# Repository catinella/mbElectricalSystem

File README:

#-----------------------------------------------------------------------------------------------------------------------------------
     __  __       _             _     _ _          _____ _           _        _           _   ____            _                 
    |  \/  | ___ | |_ ___  _ __| |__ (_) | _____  | ____| | ___  ___| |_ _ __(_) ___ __ _| | / ___| _   _ ___| |_ ___ _ __ ___  
    | |\/| |/ _ \| __/ _ \| '__| '_ \| | |/ / _ \ |  _| | |/ _ \/ __| __| '__| |/ __/ _` | | \___ \| | | / __| __/ _ \ '_ ` _ \ 
    | |  | | (_) | || (_) | |  | |_) | |   <  __/ | |___| |  __/ (__| |_| |  | | (_| (_| | |  ___) | |_| \__ \ ||  __/ | | | | |
    |_|  |_|\___/ \__\___/|_|  |_.__/|_|_|\_\___| |_____|_|\___|\___|\__|_|  |_|\___\__,_|_| |____/ \__, |___/\__\___|_| |_| |_|
                                                                                                    |___/                       
#-----------------------------------------------------------------------------------------------------------------------------------

Description:
	This project (MBES) aims to realize a generic motorbike electric system you can use on any old motorbike.
	The system manages the following devices:
		- High light and down light
		- Left and right turn indicators
		- Additional (high power) light
		- Horn
		- Neutral, left/right indicators, high/down light... LEDs
		- STOP light
		- Engine start button
		- Motorbike (and engine) OFF switch
		- Decompressor
		- External cockpit power-connector
		- Cockpit's leds

	The system provides the following features
		- Checking for decompressor command
		  The system does not allow the engine to run, before the decompressor command has been activated

		- Direction indicator blinking
		  Common blinking for the yellow indicator

		- Resistor key
		  In order to turn-on the motorbike, the driver must insert a valid resistor key. After the autentication the key
		  can be also removed. It is very usefull for off-road using. 

		- Parking mode
		  To set the motorbike turned-off but with the normal-light-on and the indicators blinking, you have to put the
		  motorbile stopped on its lateral stand, set the engine swith to off, and turn the normal-light on
	
	Security rules:
		- Byke stand
		  if the motorcycle stand is downn when the engine is connected to the wheels, the the engine will be stopped

		- Decompressor command
		  If the motorcycle is running and the driver will push the decompressor command, then the engine will be stopped

Info about this version:
	This branch is based on ESP32 MCU. This chip is a powerful and very low-price device and it allowed me to reduce the PCB
	size. At the moment, I am using the ESP32 devkit device because welder this chip is a bit difficult operation.

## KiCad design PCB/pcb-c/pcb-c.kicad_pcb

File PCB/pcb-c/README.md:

## 1.0 Files

| Files/Directories | Description             |
|-------------------|-------------------------|
| pcb-c.kicad_sch   | Electrical schematic    |
| pcb-c.kicad_pcb   | PCB                     |

(*) This project is covered by the GPL-3. Please, read that file for further information

## 2.0 Description:
This folder contains all files you need to build and/or modify the PCB placed in the rear side of the (DR350) motorbike.
This circuit is a small power stage for the rear turn indicators, brake light, and position light. Because all lights
are available in LED format, the power stage is set to provide maximum 500mA (6W) per device.

## 2.1 Internals:
In order to fit this device into the rear section of the DR350, I tried to reduce the required space as much as possible.
For this reason, conventional fuses have been replaced by [MSMF050](https://www.bourns.com/docs/product-datasheets/mf-msmf.pdf)
PTC Resettable Fuses.

All the power-stage outputs are equivalent, but one of them is dedicated to the motorbike's starter relay. This type of relay
can have a relatively large coil and may generate a significant voltage spike when switched off. For this reason, I added a
[M7 Rectifiers Diode](https://diotec.com/request/datasheet/m1.pdf) as a flyback diode.

## 3.0 PCB Layout
The following image shows the intended final PCB layout.

## 4.0 Connections
The following diagram shows how to build the cables used to connect the PCB to the other motorbike components.

### 4.1 External connectors
In the left side of the scheme you can see the cables you have to connect with the PCB (pcb-b) in the front side of the
motorcycle. The 3-ways cable of them is used to provide the battery energy to main controller device (in the front-side),
for this reason the selected connector is a 
[Receptacle Terminal Housing, 3 Position, 6.3 mm](https://www.te.com/en/product-180941.html) one. The selected FASTON terminals
can support currents up to 25A

The 6 ways cable, in the scheme left side, has to communicate data from the controller device to the rear power stage.
It has to support a very low current. So, I selected a
[2.8mm (.110") series connectors](https://www.corsa-technic.com/item.php?item_id=222&category_id=53&manufacturer_id=44).
They are very common in automotive applications, you can find all the series producted by other vendors. To get a clear
idea of them I post here a drawing of the cables.

### 4.2 Internal connectors
The main internal connector is a typical [10-pin dual-row connector](https://www.molex.com/en-us/products/part-detail/702461004)
PCB-side one, but the associated plug is not the one that is typically one used for the flat cables. In fact, its wires are not
connected to the same port: 5 pins are connected to the 6-ways external connector, and 4 are connected to the power 3-ways cable.
For this reason you need a different connector where you can crimp every pin to a single wires. Te follow math with the requirements:
[MOLEX 10pin plug](https://www.molex.com/en-us/products/part-detail/22552101?display=pdf&utm_source=M2X&utm_medium=api&utm_campaign=api&utm_id=M2X_API?utm_source=M2X&utm_medium=api&utm_campaign=api&utm_id=M2X_API)
[MOLEX contacts](https://www.molex.com/en-us/products/part-detail/16020102?display=pdf&utm_source=M2X&utm_medium=api&utm_campaign=api&utm_id=M2X_API?utm_source=M2X&utm_medium=api&utm_campaign=api&utm_id=M2X_API)

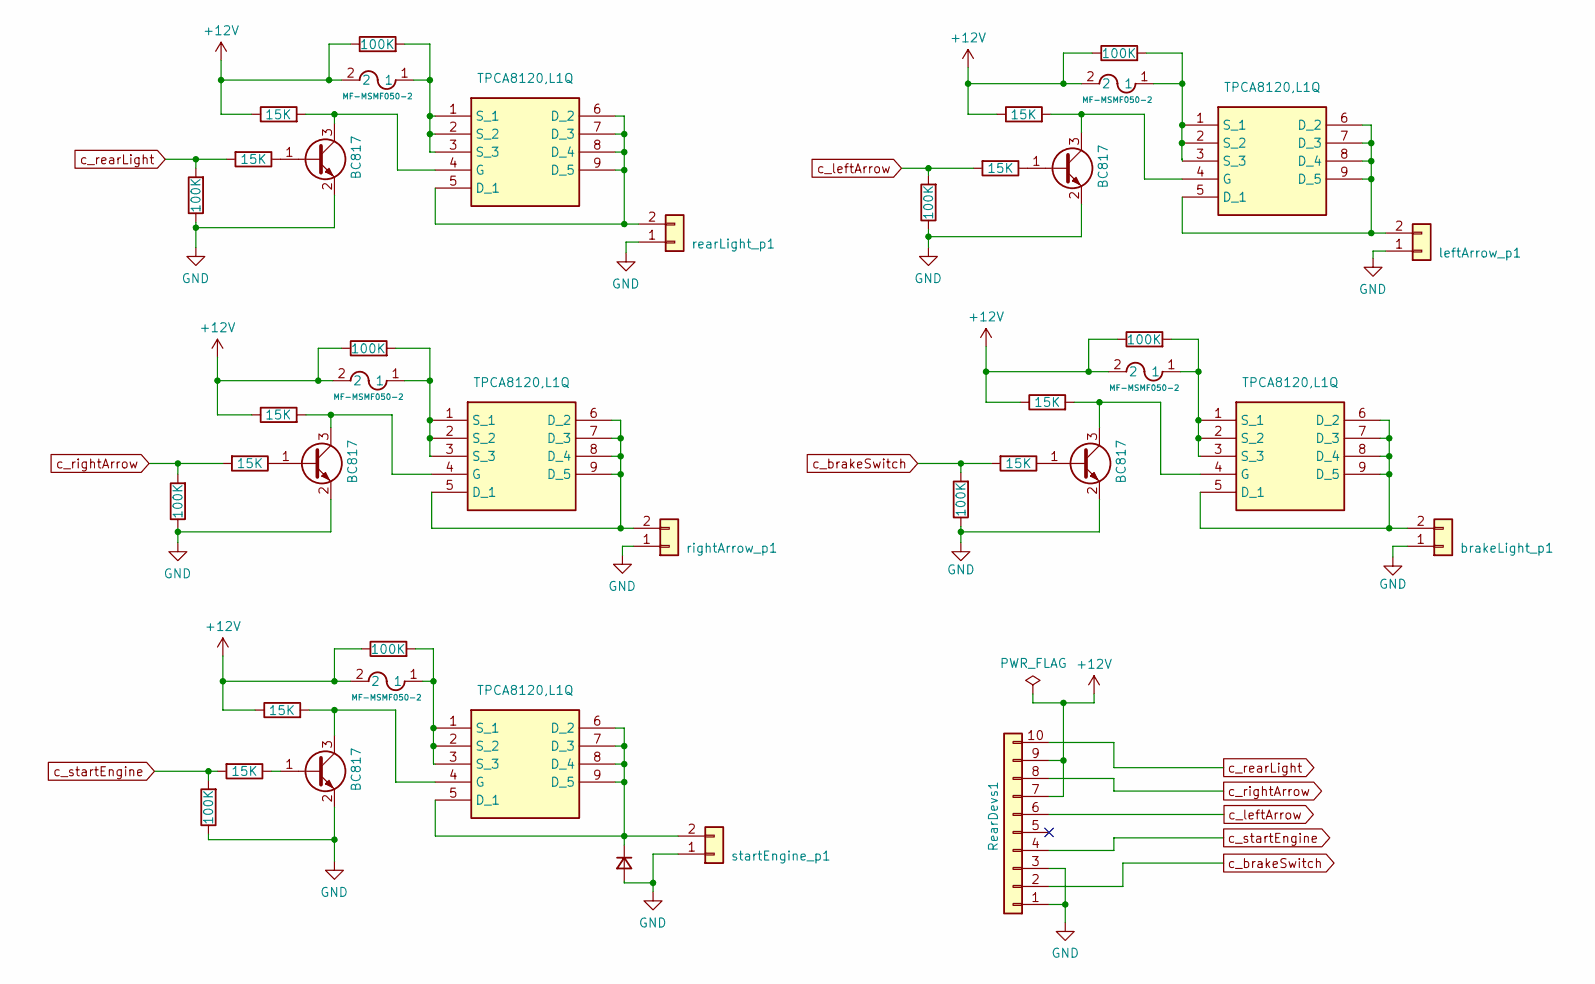
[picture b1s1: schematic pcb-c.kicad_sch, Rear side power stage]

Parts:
D1: M7; D_2114_3652Metric_Pad1.85x3.75mm_HandSolder
F1, F2, F3, F4, F5: MF-MSMF050-2; FUSE_F050-2
Q1, Q3, Q4, Q6, Q8: BC817; SOT-23
Q2, Q5, Q7, Q9, Q13: TPCA8120,L1Q; TPH4R003NLL1Q; Manufacturer_Part_Number TPCA8120,L1Q; Mouser Part Number 757-TPCA8120L1Q
R1, R3, R6, R8, R11, R12, R15, R16, R19, R21: 100K; R_1206_3216Metric
R2, R4, R5, R7, R9, R10, R13, R14, R17, R18: 15K; R_1206_3216Metric
RearDevs1: Conn_01x10; PinHeader_2x05_P2.54mm_Vertical
brakeLight_p1: Conn_01x02; PinHeader_1x02_P2.54mm_Vertical
leftArrow_p1: Conn_01x02; PinHeader_1x02_P2.54mm_Vertical
rearLight_p1: Conn_01x02; PinHeader_1x02_P2.54mm_Vertical
rightArrow_p1: Conn_01x02; PinHeader_1x02_P2.54mm_Vertical
startEngine_p1: Conn_01x02; PinHeader_1x02_P2.54mm_Vertical

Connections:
+12V: F1.2, F2.2, F3.2, F4.2, F5.2, R2.1, R3.1, R5.1, R6.1, R10.1, R11.1, R14.1, R15.1, R18.1, R19.1, RearDevs1.7, RearDevs1.9
GND: D1.2 (A), Q1.2 (E), Q3.2 (E), Q4.2 (E), Q6.2 (E), Q8.2 (E), R1.1, R8.1, R12.1, R16.1, R21.1, RearDevs1.1, RearDevs1.3, brakeLight_p1.1, leftArrow_p1.1, rearLight_p1.1, rightArrow_p1.1, startEngine_p1.1
unnamed: D1.1 (K), Q5.5 (D_1), Q5.6 (D_2), Q5.7 (D_3), Q5.8 (D_4), Q5.9 (D_5), startEngine_p1.2
unnamed: Q1.1 (B), R4.1
unnamed: Q1.3 (C), Q2.4 (G), R5.2
unnamed: Q2.5 (D_1), Q2.6 (D_2), Q2.7 (D_3), Q2.8 (D_4), Q2.9 (D_5), brakeLight_p1.2
unnamed: F2.1, Q2.1 (S_1), Q2.2 (S_2), Q2.3 (S_3), R6.2
unnamed: Q3.1 (B), R7.1
unnamed: Q4.1 (B), R9.1
unnamed: Q4.3 (C), Q5.4 (G), R10.2
unnamed: F5.1, Q5.1 (S_1), Q5.2 (S_2), Q5.3 (S_3), R3.2
unnamed: Q6.1 (B), R13.1
unnamed: Q6.3 (C), Q7.4 (G), R14.2
unnamed: Q7.5 (D_1), Q7.6 (D_2), Q7.7 (D_3), Q7.8 (D_4), Q7.9 (D_5), leftArrow_p1.2
unnamed: F4.1, Q7.1 (S_1), Q7.2 (S_2), Q7.3 (S_3), R15.2
unnamed: Q8.1 (B), R17.1
unnamed: Q8.3 (C), Q9.4 (G), R18.2
unnamed: Q9.5 (D_1), Q9.6 (D_2), Q9.7 (D_3), Q9.8 (D_4), Q9.9 (D_5), rightArrow_p1.2
unnamed: F1.1, Q9.1 (S_1), Q9.2 (S_2), Q9.3 (S_3), R11.2
unnamed: Q13.5 (D_1), Q13.6 (D_2), Q13.7 (D_3), Q13.8 (D_4), Q13.9 (D_5), rearLight_p1.2
unnamed: Q3.3 (C), Q13.4 (G), R2.2
unnamed: F3.1, Q13.1 (S_1), Q13.2 (S_2), Q13.3 (S_3), R19.2
c_brakeSwitch: R1.2, R4.2, RearDevs1.2
c_leftArrow: R12.2, R13.2, RearDevs1.6
c_rearLight: R7.2, R21.2, RearDevs1.10
c_rightArrow: R16.2, R17.2, RearDevs1.8
c_startEngine: R8.2, R9.2, RearDevs1.4

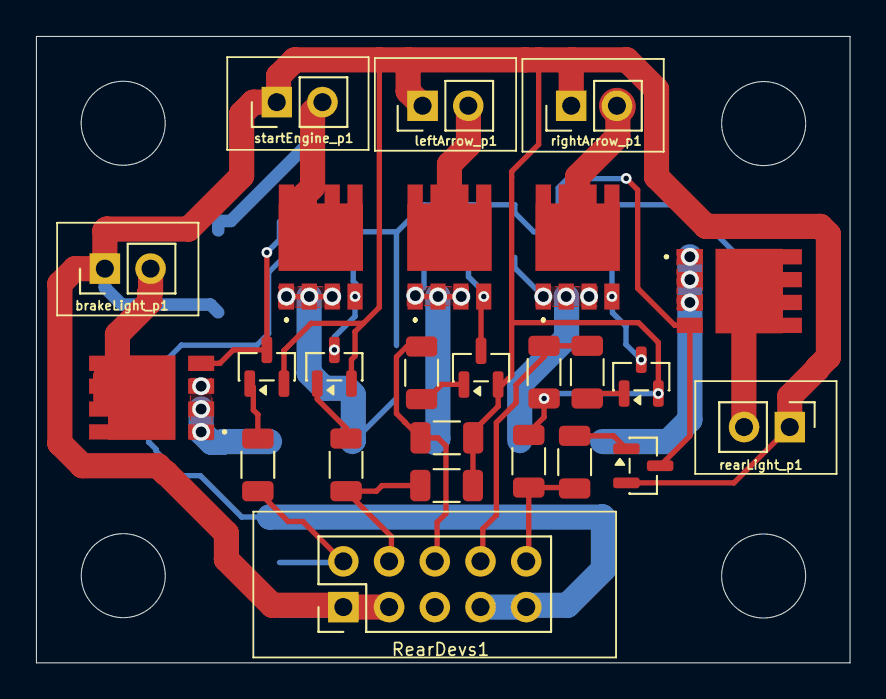
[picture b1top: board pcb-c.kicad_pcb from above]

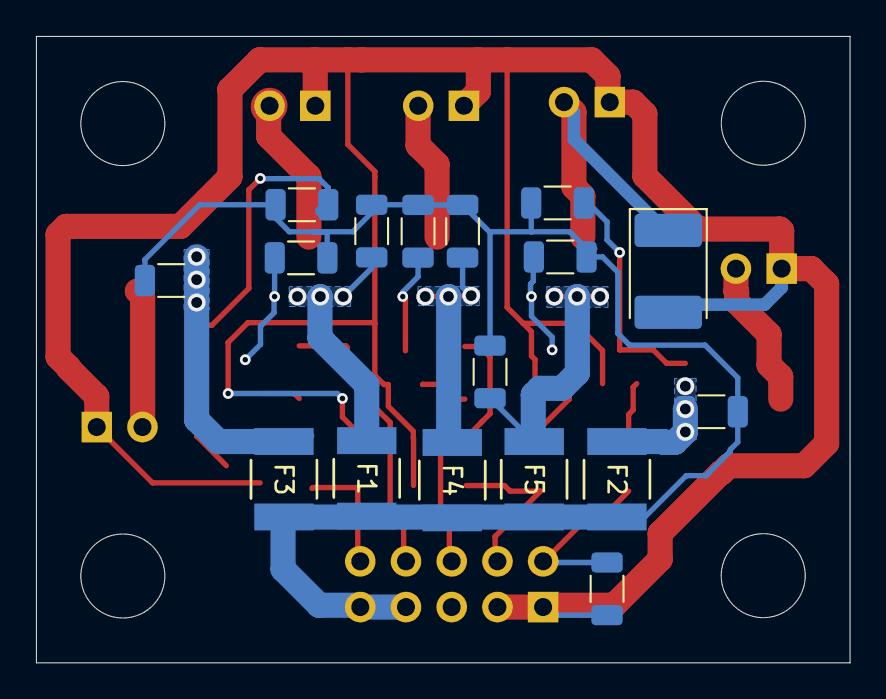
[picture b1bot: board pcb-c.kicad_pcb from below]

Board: 2 copper layers, 45.2 x 34.8 mm, 42 parts (17 on the bottom side), 27 nets.

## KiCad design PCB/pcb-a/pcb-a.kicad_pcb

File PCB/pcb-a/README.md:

## 1.0 Files

|        Files/Directories       | Description                          |
|--------------------------------|--------------------------------------|
| pcb-a.kicad_sch                | Main electrical schematic            |
| mbes_pcbA_connectors.kicad_sch | Connectors electrical schematic      |
| pcb-a.kicad_pcb                | PCB                                  |

(*) This project is covered by the GPL-3. Please read that file for further information.

## 2.0 Description
This folder contains all the files you need to modify/build the PCB that implements the Motorbike Electrical System's brain. It
controls the handlebar commands (buttons, switches...) and turns on/off the services according to its policies.

### 2.1 The Microcontroller Unit
In order to implement the motorbike's services management, I have chosen the 
[ESP32-S2](https://documentation.espressif.com/esp32-s2_datasheet_en.pdf) MCU produced by Espressif. I selected this chip for the
following reasons:

- It has **43 programmable GPIOs**. This allows me to manage all I/O lines without an external bus expander (e.g. MCP23016). 
- Its core is an Xtensa® **single-core 32-bit LX7 microprocessor (240 MHz)**. It is faster than what is needed.
- ROM = 128 KB and **SRAM = 320 KB**. Adequate also for future implementations (e.g. display management).
- I2C and SPI ports. They will be necessary for future **CAN bus** implementation.
- **ESP-IDF** framework. It is a large and powerful framework that allows you to develop even complex firmware easily.
- Embedded **Wi-Fi** support. It will be needed for future implementations (mobile cockpit).
- **ADC**. Required for resistive key authentication.
- It is a powerful but cheap device: less than 4 euros.

### 2.2 MCU vs DevKit
The ESP32-S2, like all modern MCUs, is available in SMD but not in a THT package. Unfortunately, its SMD package (like most modern
MCUs) is difficult to solder, too difficult for me. So, for now, I have used the official development kit 
[ESP32-S2-DevKitM-1](https://docs.espressif.com/projects/esp-idf/en/v5.2.1/esp32s2/hw-reference/esp32s2/user-guide-devkitm-1-v1.html)
produced by Espressif. It is widely available on the market and costs less than 10 euros.

### 2.3 Cables and internal connectors
For every cable starting from this PCB, a 2.54mm pin header socket is provided. This type of connector can support up to 2.5A of
current. This means it can handle 1.5A without problems, which is absolutely higher than what is needed here.  
On the PCB you can find the following sockets:

1) Two [10-pin dual-row connectors](https://www.molex.com/en-us/products/part-detail/702461004?display=pdf) used for communication
   between the two PCBs on the motorbike's front side.
2) Two single-row connectors used to connect the left and right handlebar controls (lights, direction indicators, horn,
   engine on/off...).
3) One 8-pin single-row connector to control the rear-side power stage (pcb-c).
4) Many 2-pin single-row connectors to connect some switches (PowerOff, additionalLight, decompressor...).
5) One 4-pin single-row connector for the resistive key socket (4 of 6 pins).

Unfortunately, I have not found documentation for 2.54 mm single-row pin headers, so I took the following photo:

The cables connected to the **#1** type socket are for internal communication only, and the current flowing through them is very low (<100 mA).  
Thanks to this, you don't need to solder the connector pins; you can use a 
[10-pin flat cable](https://www.we-online.com/components/products/datasheet/63911015521CAB.pdf) and
the [YTH214 Crimping Tool IDC](https://docs.rs-online.com/8d29/A700000009783991.pdf) to crimp the connectors.

All other connectors (except the one for the resistive key lock) are for external links, so the cable must be sufficiently robust.  
For this reason, you can use AWG24 cable: it has a 0.22 mm² cross-section and supports up to 2 A, much more than needed.

### 2.4 External connectors
In order to connect the handlebar electrical controls (buttons/switches), I selected 2.8 mm tab terminal system connectors.  
These connectors are widely used in automotive applications; for this reason, you can find them referred to as "2.8 mm automotive connectors".  
You can easily buy them as kits, even on Amazon.  
Each (2.8 mm) pin of this type can handle 10 A without problems.

In the following picture you can see the 6-ways connector diagram used for the left/right hand-bar's controls

**Left connector pin map:**

1) GND
2) Left turn indicator
3) Low-beam light
4) High-beam light
5) Right turn indicator
6) Horn
	                              
**Right connector pin map:**

1) GND
2) GND
3) Brake control switch
4) Engine START button
5) Engine OFF
6) Engine ON

### 2.5 How to connect the front-side device with the rear-side one

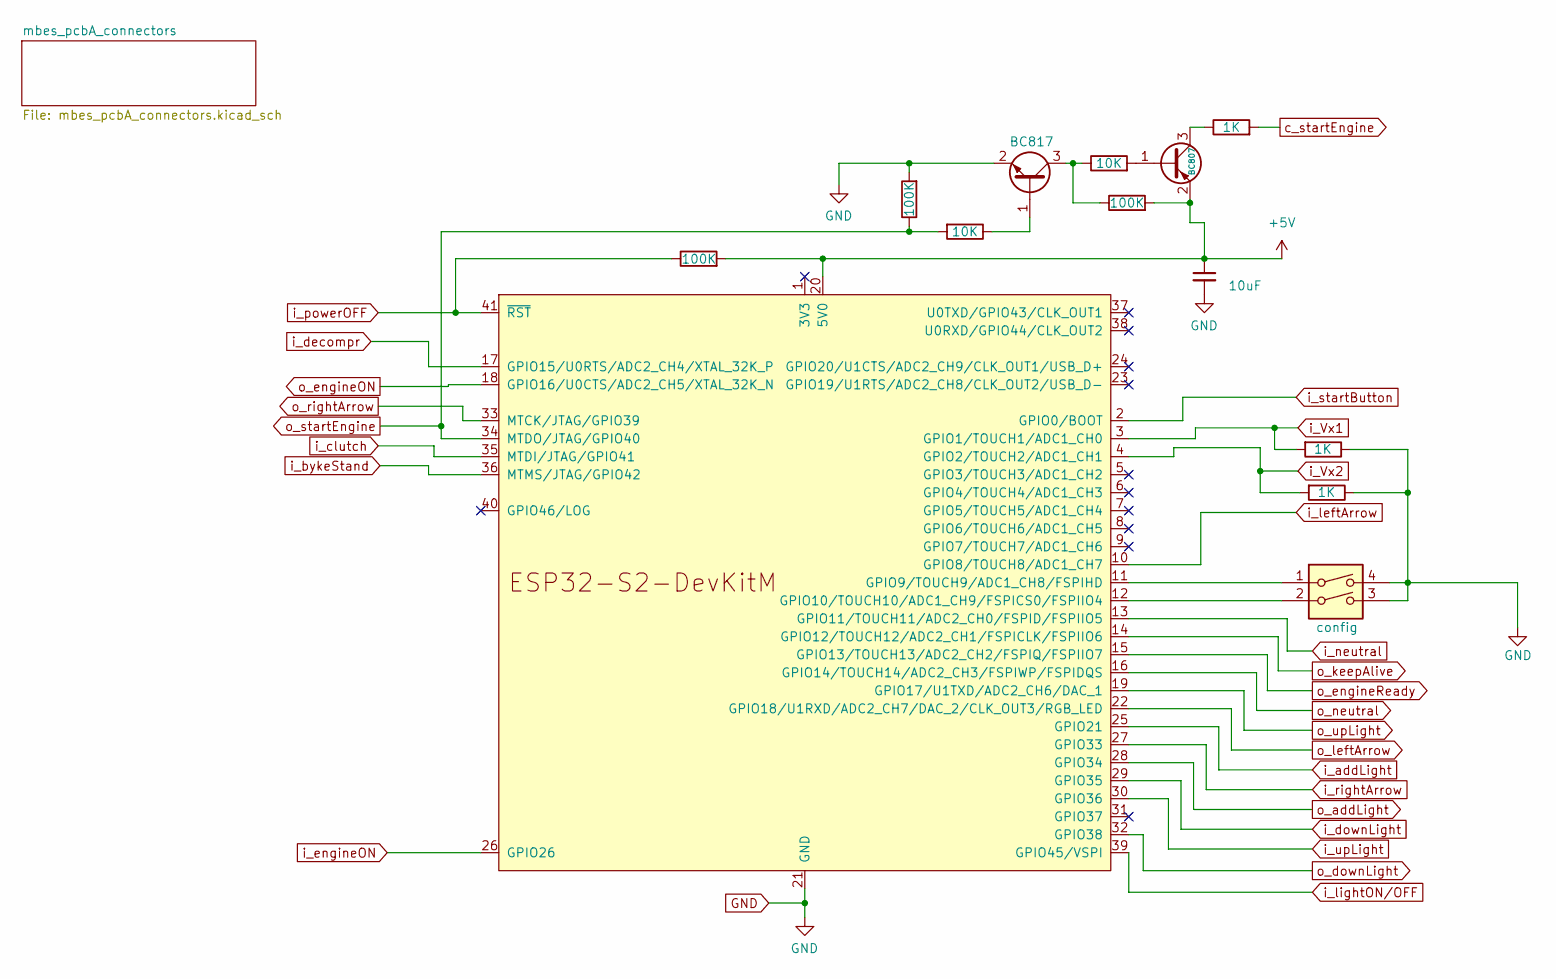
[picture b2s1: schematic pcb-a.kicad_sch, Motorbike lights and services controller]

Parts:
C1: 10uF; CP_Radial_D6.3mm_P2.50mm
Q1: BC807; SOT-23
Q3: BC817; SOT-23
R2, R6, R21: 100K; R_1206_3216Metric
R3, R4, R15: 1K; R_1206_3216Metric
R7, R10: 10K; R_1206_3216Metric
SW1: config; SW_DIP_SPSTx02_Slide_6.7x6.64mm_W7.62mm_P2.54mm_LowProfile
U1: ESP32-S2-DevKitM

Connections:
+5V: C1.1, Q1.2 (E), R2.2, R6.2, U1.20 (5V0); also elsewhere on the board
GND: C1.2, Q3.2 (E), R3.1, R4.1, R21.2, SW1.3, SW1.4, U1.21 (GND), U1.42 (GND); also elsewhere on the board
unnamed: Q1.1 (B), R10.2
unnamed: Q1.3 (C), R15.1
unnamed: Q3.1 (B), R7.1
unnamed: Q3.3 (C), R6.1, R10.1
unnamed: SW1.1, U1.11 (GPIO9/TOUCH9/ADC1_CH8/FSPIHD)
unnamed: SW1.2, U1.12 (GPIO10/TOUCH10/ADC1_CH9/FSPICS0/FSPIIO4)
c_startEngine: R15.2; also elsewhere on the board
i_Vx1: R3.2, U1.3 (GPIO1/TOUCH1/ADC1_CH0); also elsewhere on the board
i_Vx2: R4.2, U1.4 (GPIO2/TOUCH2/ADC1_CH1); also elsewhere on the board
i_addLight: U1.25 (GPIO21); also elsewhere on the board
i_bykeStand: U1.36 (MTMS/JTAG/GPIO42); also elsewhere on the board
i_clutch: U1.35 (MTDI/JTAG/GPIO41); also elsewhere on the board
i_decompr: U1.17 (GPIO15/U0RTS/ADC2_CH4/XTAL_32K_P); also elsewhere on the board
i_downLight: U1.29 (GPIO35); also elsewhere on the board
i_engineON: U1.26 (GPIO26); also elsewhere on the board
i_leftArrow: U1.10 (GPIO8/TOUCH8/ADC1_CH7); also elsewhere on the board
i_lightON/OFF: U1.39 (GPIO45/VSPI); also elsewhere on the board
i_neutral: U1.13 (GPIO11/TOUCH11/ADC2_CH0/FSPID/FSPIIO5); also elsewhere on the board
i_powerOFF: R2.1, U1.41 (~RST); also elsewhere on the board
i_rightArrow: U1.27 (GPIO33); also elsewhere on the board
i_startButton: U1.2 (GPIO0/BOOT); also elsewhere on the board
i_upLight: U1.30 (GPIO36); also elsewhere on the board
o_addLight: U1.28 (GPIO34); also elsewhere on the board
o_downLight: U1.32 (GPIO38); also elsewhere on the board
o_engineON: U1.18 (GPIO16/U0CTS/ADC2_CH5/XTAL_32K_N); also elsewhere on the board
o_engineReady: U1.15 (GPIO13/TOUCH13/ADC2_CH2/FSPIQ/FSPIIO7); also elsewhere on the board
o_keepAlive: U1.14 (GPIO12/TOUCH12/ADC2_CH1/FSPICLK/FSPIIO6); also elsewhere on the board
o_leftArrow: U1.22 (GPIO18/U1RXD/ADC2_CH7/DAC_2/CLK_OUT3/RG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); also elsewhere on the board
o_neutral: U1.16 (GPIO14/TOUCH14/ADC2_CH3/FSPIWP/FSPIDQS); also elsewhere on the board
o_rightArrow: U1.33 (MTCK/JTAG/GPIO39); also elsewhere on the board
o_startEngine: R7.2, R21.1, U1.34 (MTDO/JTAG/GPIO40)
o_upLight: U1.19 (GPIO17/U1TXD/ADC2_CH6/DAC_1); also elsewhere on the board

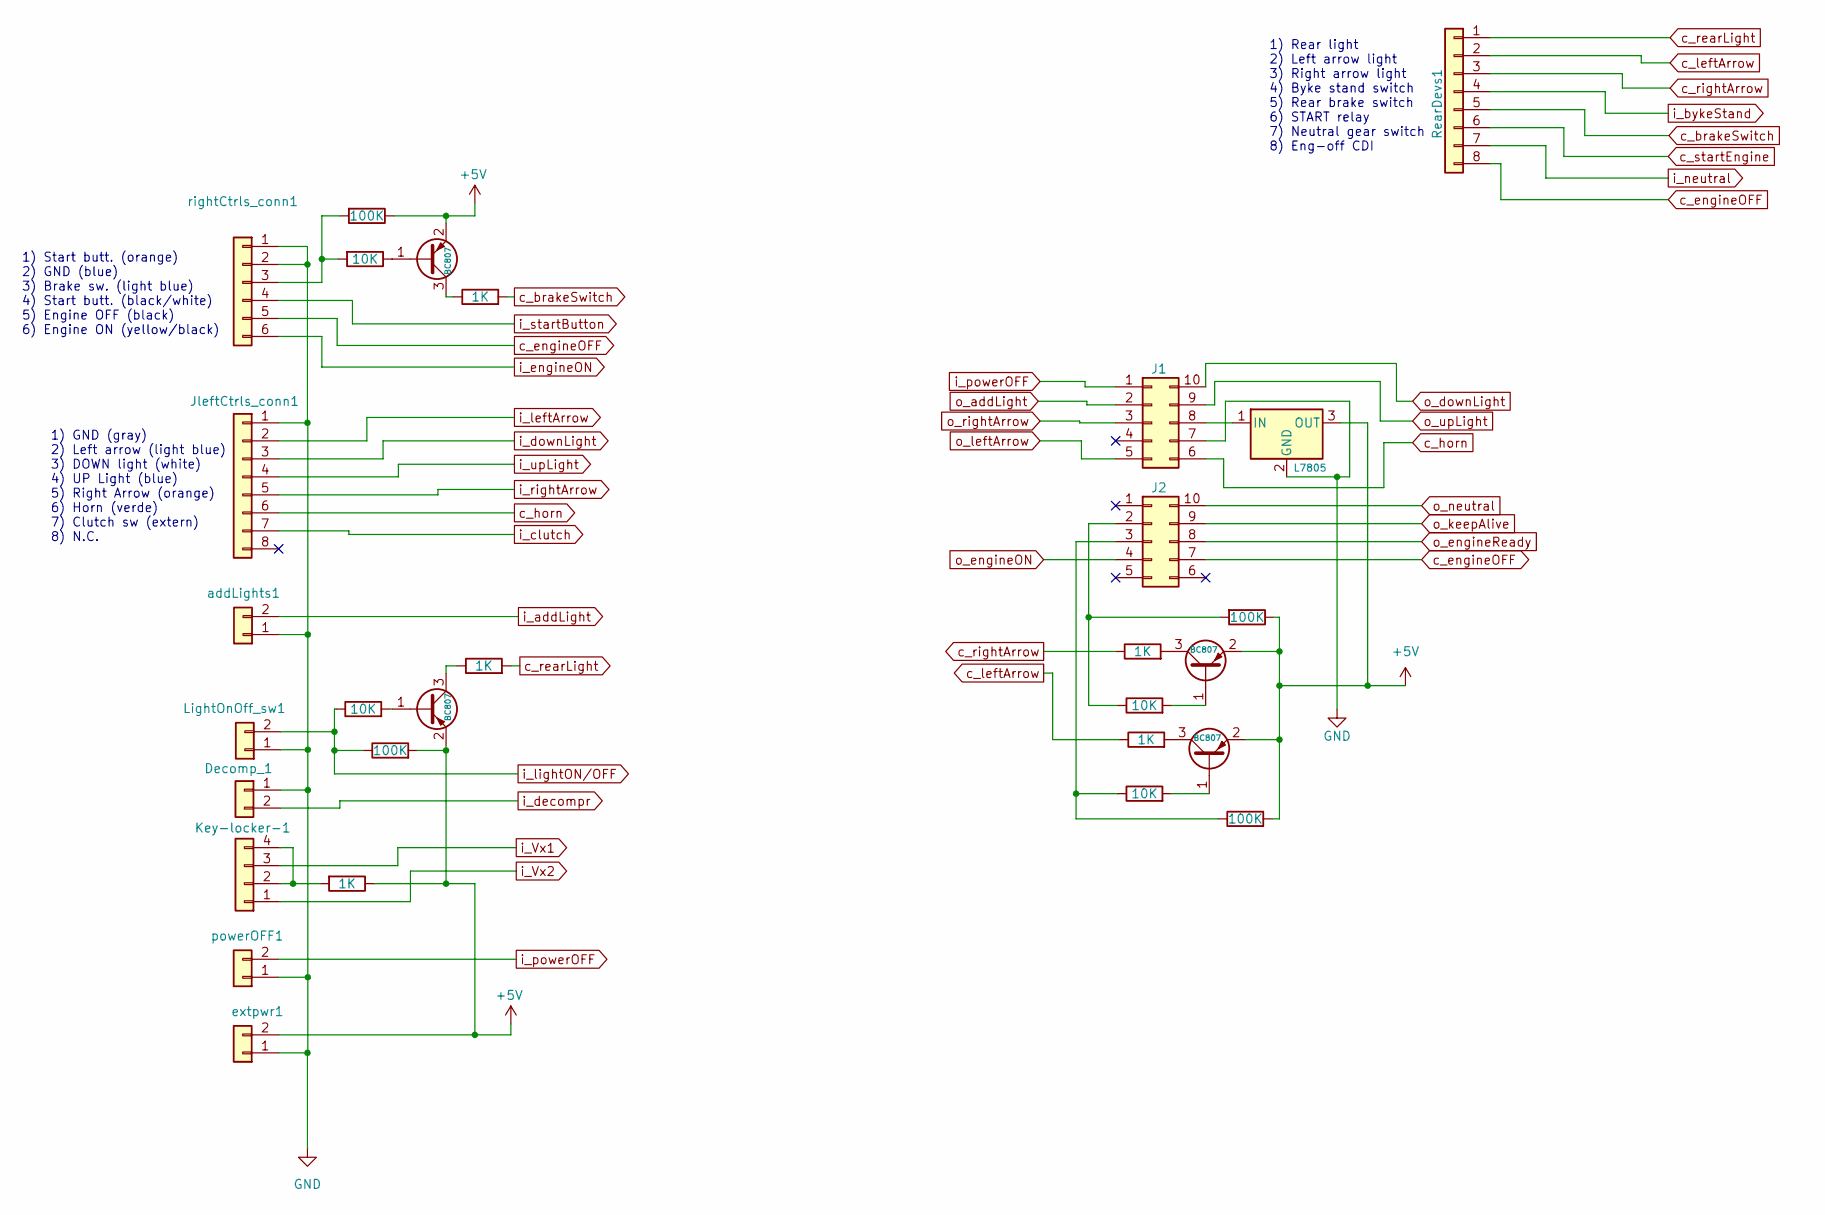
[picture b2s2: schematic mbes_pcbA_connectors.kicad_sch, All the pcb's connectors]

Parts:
Decomp_1: Conn_01x02; PinHeader_1x02_P2.54mm_Vertical
J1, J2: Conn_02x05_Counter_Clockwise; PinHeader_2x05_P2.54mm_Vertical
JleftCtrls_conn1: Conn_01x08; PinHeader_1x08_P2.54mm_Vertical
Key-locker-1: Conn_01x04; PinHeader_1x04_P2.54mm_Vertical
LightOnOff_sw1: Conn_01x02; PinHeader_1x02_P2.54mm_Vertical
Q2, Q4, Q5, Q6: BC807; SOT-23
R1, R11, R12, R13, R20: 1K; R_1206_3216Metric
R5, R8, R9, R18: 10K; R_1206_3216Metric
R14, R16, R17, R19: 100K; R_1206_3216Metric
RearDevs1: Conn_01x08; PinHeader_1x08_P2.54mm_Vertical
U3: L7805; TO-220-3_Vertical
addLights1: Conn_01x02; PinHeader_1x02_P2.54mm_Vertical
extpwr1: Conn_01x02; PinHeader_1x02_P2.54mm_Vertical
powerOFF1: Conn_01x02; PinHeader_1x02_P2.54mm_Vertical
rightCtrls_conn1: Conn_01x06; PinHeader_1x06_P2.54mm_Vertical

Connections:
+5V: Q2.2 (E), Q4.2 (E), Q5.2 (E), Q6.2 (E), R1.1, R14.1, R16.1, R17.2, R19.2, U3.3 (OUT), extpwr1.2; also elsewhere on the board
GND: Decomp_1.1, J1.7, JleftCtrls_conn1.1, LightOnOff_sw1.1, U3.2 (GND), addLights1.1, extpwr1.1, powerOFF1.1, rightCtrls_conn1.1, rightCtrls_conn1.2; also elsewhere on the board
unnamed: J1.8, U3.1 (IN)
unnamed: J2.2, R5.1, R16.2
unnamed: J2.3, R8.1, R17.1
unnamed: Key-locker-1.2, Key-locker-1.4, R1.2
unnamed: Q2.1 (B), R5.2
unnamed: Q2.3 (C), R12.2
unnamed: Q4.1 (B), R8.2
unnamed: Q4.3 (C), R11.2
unnamed: Q5.1 (B), R9.1
unnamed: Q5.3 (C), R13.1
unnamed: Q6.1 (B), R18.2
unnamed: Q6.3 (C), R20.1
unnamed: R9.2, R14.2, rightCtrls_conn1.3
c_brakeSwitch: R13.2, RearDevs1.5
c_engineOFF: J2.7, RearDevs1.8, rightCtrls_conn1.5
c_horn: J1.6, JleftCtrls_conn1.6
c_leftArrow: R11.1, RearDevs1.2
c_rearLight: R20.2, RearDevs1.1
c_rightArrow: R12.1, RearDevs1.3
c_startEngine: RearDevs1.6; also elsewhere on the board
i_Vx1: Key-locker-1.3; also elsewhere on the board
i_Vx2: Key-locker-1.1; also elsewhere on the board
i_addLight: addLights1.2; also elsewhere on the board
i_bykeStand: RearDevs1.4; also elsewhere on the board
i_clutch: JleftCtrls_conn1.7; also elsewhere on the board
i_decompr: Decomp_1.2; also elsewhere on the board
i_downLight: JleftCtrls_conn1.3; also elsewhere on the board
i_engineON: rightCtrls_conn1.6; also elsewhere on the board
i_leftArrow: JleftCtrls_conn1.2; also elsewhere on the board
i_lightON/OFF: LightOnOff_sw1.2, R18.1, R19.1; also elsewhere on the board
i_neutral: RearDevs1.7; also elsewhere on the board
i_powerOFF: J1.1, powerOFF1.2; also elsewhere on the board
i_rightArrow: JleftCtrls_conn1.5; also elsewhere on the board
i_startButton: rightCtrls_conn1.4; also elsewhere on the board
i_upLight: JleftCtrls_conn1.4; also elsewhere on the board
o_addLight: J1.2; also elsewhere on the board
o_downLight: J1.10; also elsewhere on the board
o_engineON: J2.4; also elsewhere on the board
o_engineReady: J2.8; also elsewhere on the board
o_keepAlive: J2.9; also elsewhere on the board
o_leftArrow: J1.5; also elsewhere on the board
o_neutral: J2.10; also elsewhere on the board
o_rightArrow: J1.3; also elsewhere on the board
o_upLight: J1.9; also elsewhere on the board

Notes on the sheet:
1) Start butt. (orange) 2) GND (blue) 3) Brake sw. (light blue) 4) Start butt. (black/white) 5) Engine OFF (black) 6) Engine ON (yellow/black)
1) GND (gray) 2) Left arrow (light blue) 3) DOWN light (white) 4) UP Light (blue) 5) Right Arrow (orange) 6) Horn (verde) 7) Clutch sw (extern) 8) N.C.
1) Rear light 2) Left arrow light 3) Right arrow light 4) Byke stand switch 5) Rear brake switch 6) START relay 7) Neutral gear switch 8) Eng-off CDI

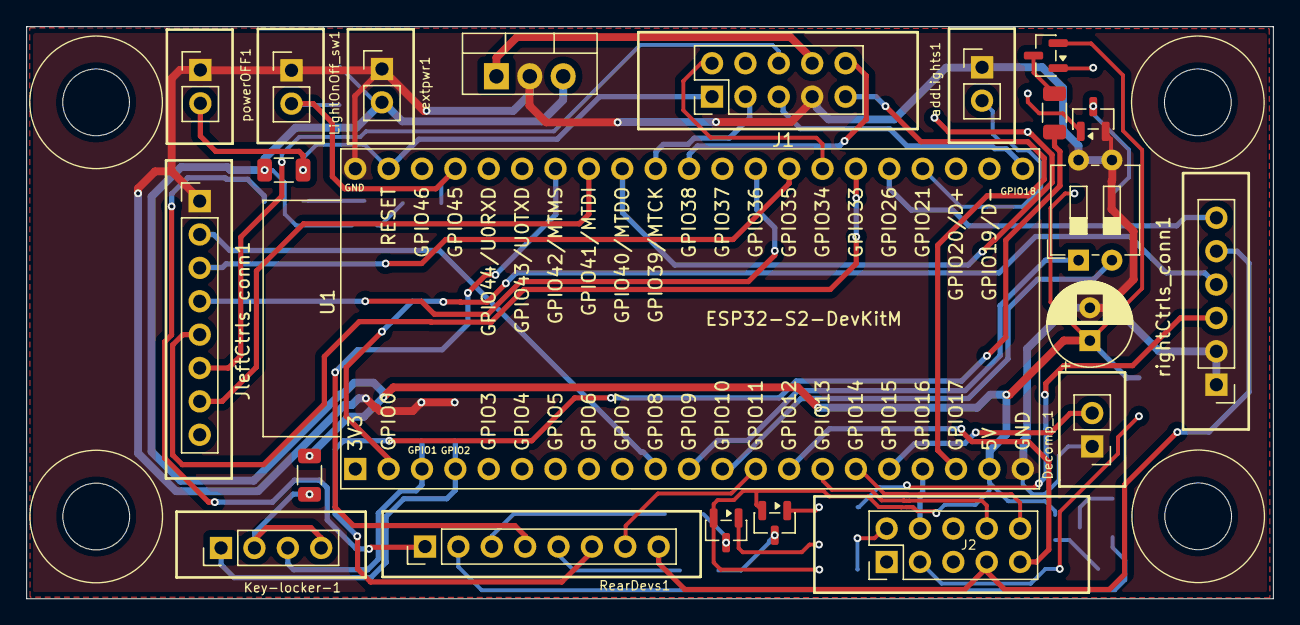
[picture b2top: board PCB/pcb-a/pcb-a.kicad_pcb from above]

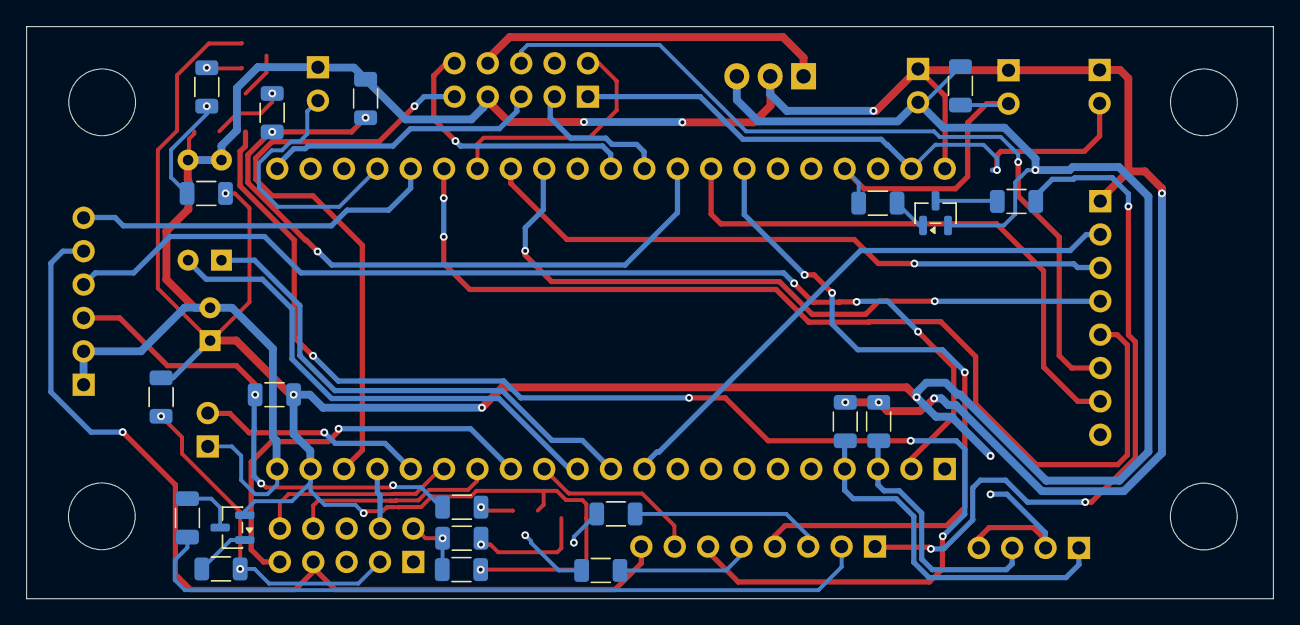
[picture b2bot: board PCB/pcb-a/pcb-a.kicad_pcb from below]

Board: 2 copper layers, 94.9 x 43.5 mm, 42 parts (20 on the bottom side), 53 nets.

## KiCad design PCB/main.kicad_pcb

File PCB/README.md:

## 1.0 Files

|       Files/Directories        | Description                          |
|--------------------------------|--------------------------------------|
| Connectors.txt                 | Cables's connectors pin-out          |
| create_fabric_files.sh         | Script to create the fabric files    |
| kicad_symbols                  | Non standard KiCAD symbols libraries |
| LICENSE.txt                    | The project's licence file (\*)      |
| pcb-a                          | Controller stage's PCB               |
| pcb-b                          | Front side power stage's PCB         |
| pcb-c                          | Rear side power stage's PCB          |
| starter_key_plug               | The schema of the resistive key      |
| images                         | The images used by this file         |

(*) This project is covered by the GPL-3. Please, read that file for further information

## 2.0 Description:
This folder contains all files you need to get and/or modify your own PCBs.
To perform these actions you need to install [KiCAD](https://www.kicad.org) software (ver >= 9.0), a free software suite for
electronic design automation (EDA).

The solution implemented in this branch (ESP32__dualPCB) is composed by three PCBs. The following table shows you their functions
and the connected devices

|         Function         |                                  Devices                                       |
|--------------------------|--------------------------------------------------------------------------------|
| Logic controller         | input buttons, switches... from hand bar and motorbike internals (eg. neutral) |
| Front side power stage   | front side services (eg. horn, front-lights, front-direction-indicators..)     |
| Rear side power stage    | rear side service (eg. stop-light, start-engine relay, rear-light...)          |

For further information about any single PCB, please, read the proper README.md file inside its folder

The following images shows you the PCB shapes they should be at the end

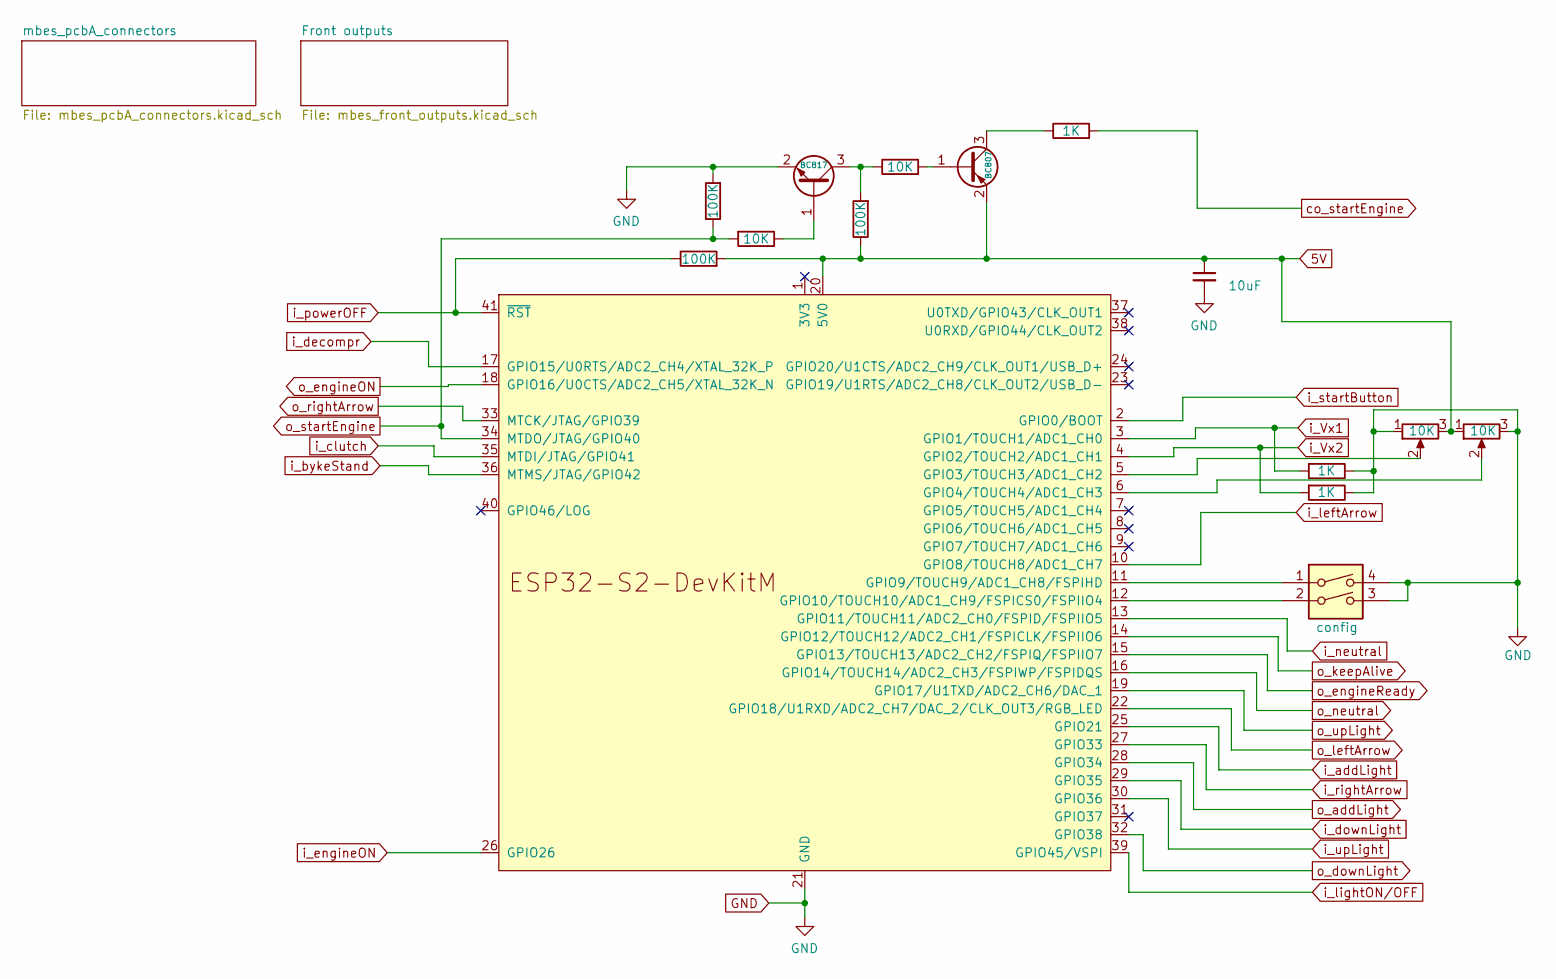
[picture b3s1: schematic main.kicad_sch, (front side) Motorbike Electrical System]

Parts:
C1: 10uF; CP_Radial_D6.3mm_P2.50mm
Q19: BC817; SOT-23
Q23: BC807; SOT-23
R1, R5, R14: 100K; R_1206_3216Metric
R2: 10K; R_1206_3216Metric
R3, R4: 1K; R_1206_3216Metric
RA49: 10K; R_1206_3216Metric
RA51: 1K; R_1206_3216Metric
RV1, RV2: 10K; Potentiometer_Bourns_3296W_Vertical
SW1: config; SW_DIP_SPSTx02_Slide_6.7x6.64mm_W7.62mm_P2.54mm_LowProfile
U1: ESP32-S2-DevKitM

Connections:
5V: C1.1, Q23.2 (E), R1.2, R5.1, RV1.3, RV2.1, U1.20 (5V0); also elsewhere on the board
GND: C1.2, Q19.2 (E), R3.1, R4.1, R14.2, RV1.1, RV2.3, SW1.3, SW1.4, U1.21 (GND), U1.42 (GND); also elsewhere on the board
unnamed: Q19.1 (B), R2.1
unnamed: Q19.3 (C), R5.2, RA49.1
unnamed: Q23.1 (B), RA49.2
unnamed: Q23.3 (C), RA51.1
unnamed: RV1.2, U1.5 (GPIO3/TOUCH3/ADC1_CH2)
unnamed: RV2.2, U1.6 (GPIO4/TOUCH4/ADC1_CH3)
unnamed: SW1.1, U1.11 (GPIO9/TOUCH9/ADC1_CH8/FSPIHD)
unnamed: SW1.2, U1.12 (GPIO10/TOUCH10/ADC1_CH9/FSPICS0/FSPIIO4)
co_startEngine: RA51.2; also elsewhere on the board
i_Vx1: R3.2, U1.3 (GPIO1/TOUCH1/ADC1_CH0); also elsewhere on the board
i_Vx2: R4.2, U1.4 (GPIO2/TOUCH2/ADC1_CH1); also elsewhere on the board
i_addLight: U1.25 (GPIO21); also elsewhere on the board
i_bykeStand: U1.36 (MTMS/JTAG/GPIO42); also elsewhere on the board
i_clutch: U1.35 (MTDI/JTAG/GPIO41); also elsewhere on the board
i_decompr: U1.17 (GPIO15/U0RTS/ADC2_CH4/XTAL_32K_P); also elsewhere on the board
i_downLight: U1.29 (GPIO35); also elsewhere on the board
i_engineON: U1.26 (GPIO26); also elsewhere on the board
i_leftArrow: U1.10 (GPIO8/TOUCH8/ADC1_CH7); also elsewhere on the board
i_lightON/OFF: U1.39 (GPIO45/VSPI); also elsewhere on the board
i_neutral: U1.13 (GPIO11/TOUCH11/ADC2_CH0/FSPID/FSPIIO5); also elsewhere on the board
i_powerOFF: R1.1, U1.41 (~RST); also elsewhere on the board
i_rightArrow: U1.27 (GPIO33); also elsewhere on the board
i_startButton: U1.2 (GPIO0/BOOT); also elsewhere on the board
i_upLight: U1.30 (GPIO36); also elsewhere on the board
o_addLight: U1.28 (GPIO34); also elsewhere on the board
o_downLight: U1.32 (GPIO38); also elsewhere on the board
o_engineON: U1.18 (GPIO16/U0CTS/ADC2_CH5/XTAL_32K_N); also elsewhere on the board
o_engineReady: U1.15 (GPIO13/TOUCH13/ADC2_CH2/FSPIQ/FSPIIO7); also elsewhere on the board
o_keepAlive: U1.14 (GPIO12/TOUCH12/ADC2_CH1/FSPICLK/FSPIIO6); also elsewhere on the board
o_leftArrow: U1.22 (GPIO18/U1RXD/ADC2_CH7/DAC_2/CLK_OUT3/RG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); also elsewhere on the board
o_neutral: U1.16 (GPIO14/TOUCH14/ADC2_CH3/FSPIWP/FSPIDQS); also elsewhere on the board
o_rightArrow: U1.33 (MTCK/JTAG/GPIO39); also elsewhere on the board
o_startEngine: R2.2, R14.1, U1.34 (MTDO/JTAG/GPIO40)
o_upLight: U1.19 (GPIO17/U1TXD/ADC2_CH6/DAC_1); also elsewhere on the board
